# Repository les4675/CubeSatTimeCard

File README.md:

Currently we have developed models from the top level overview of our time card, along with setting up the SOM. Our goal in the next few months is program the SOM to take in data from a GNSS through the CAN protcol and to fine tone the PLL with the atomic clock that we have aquired.

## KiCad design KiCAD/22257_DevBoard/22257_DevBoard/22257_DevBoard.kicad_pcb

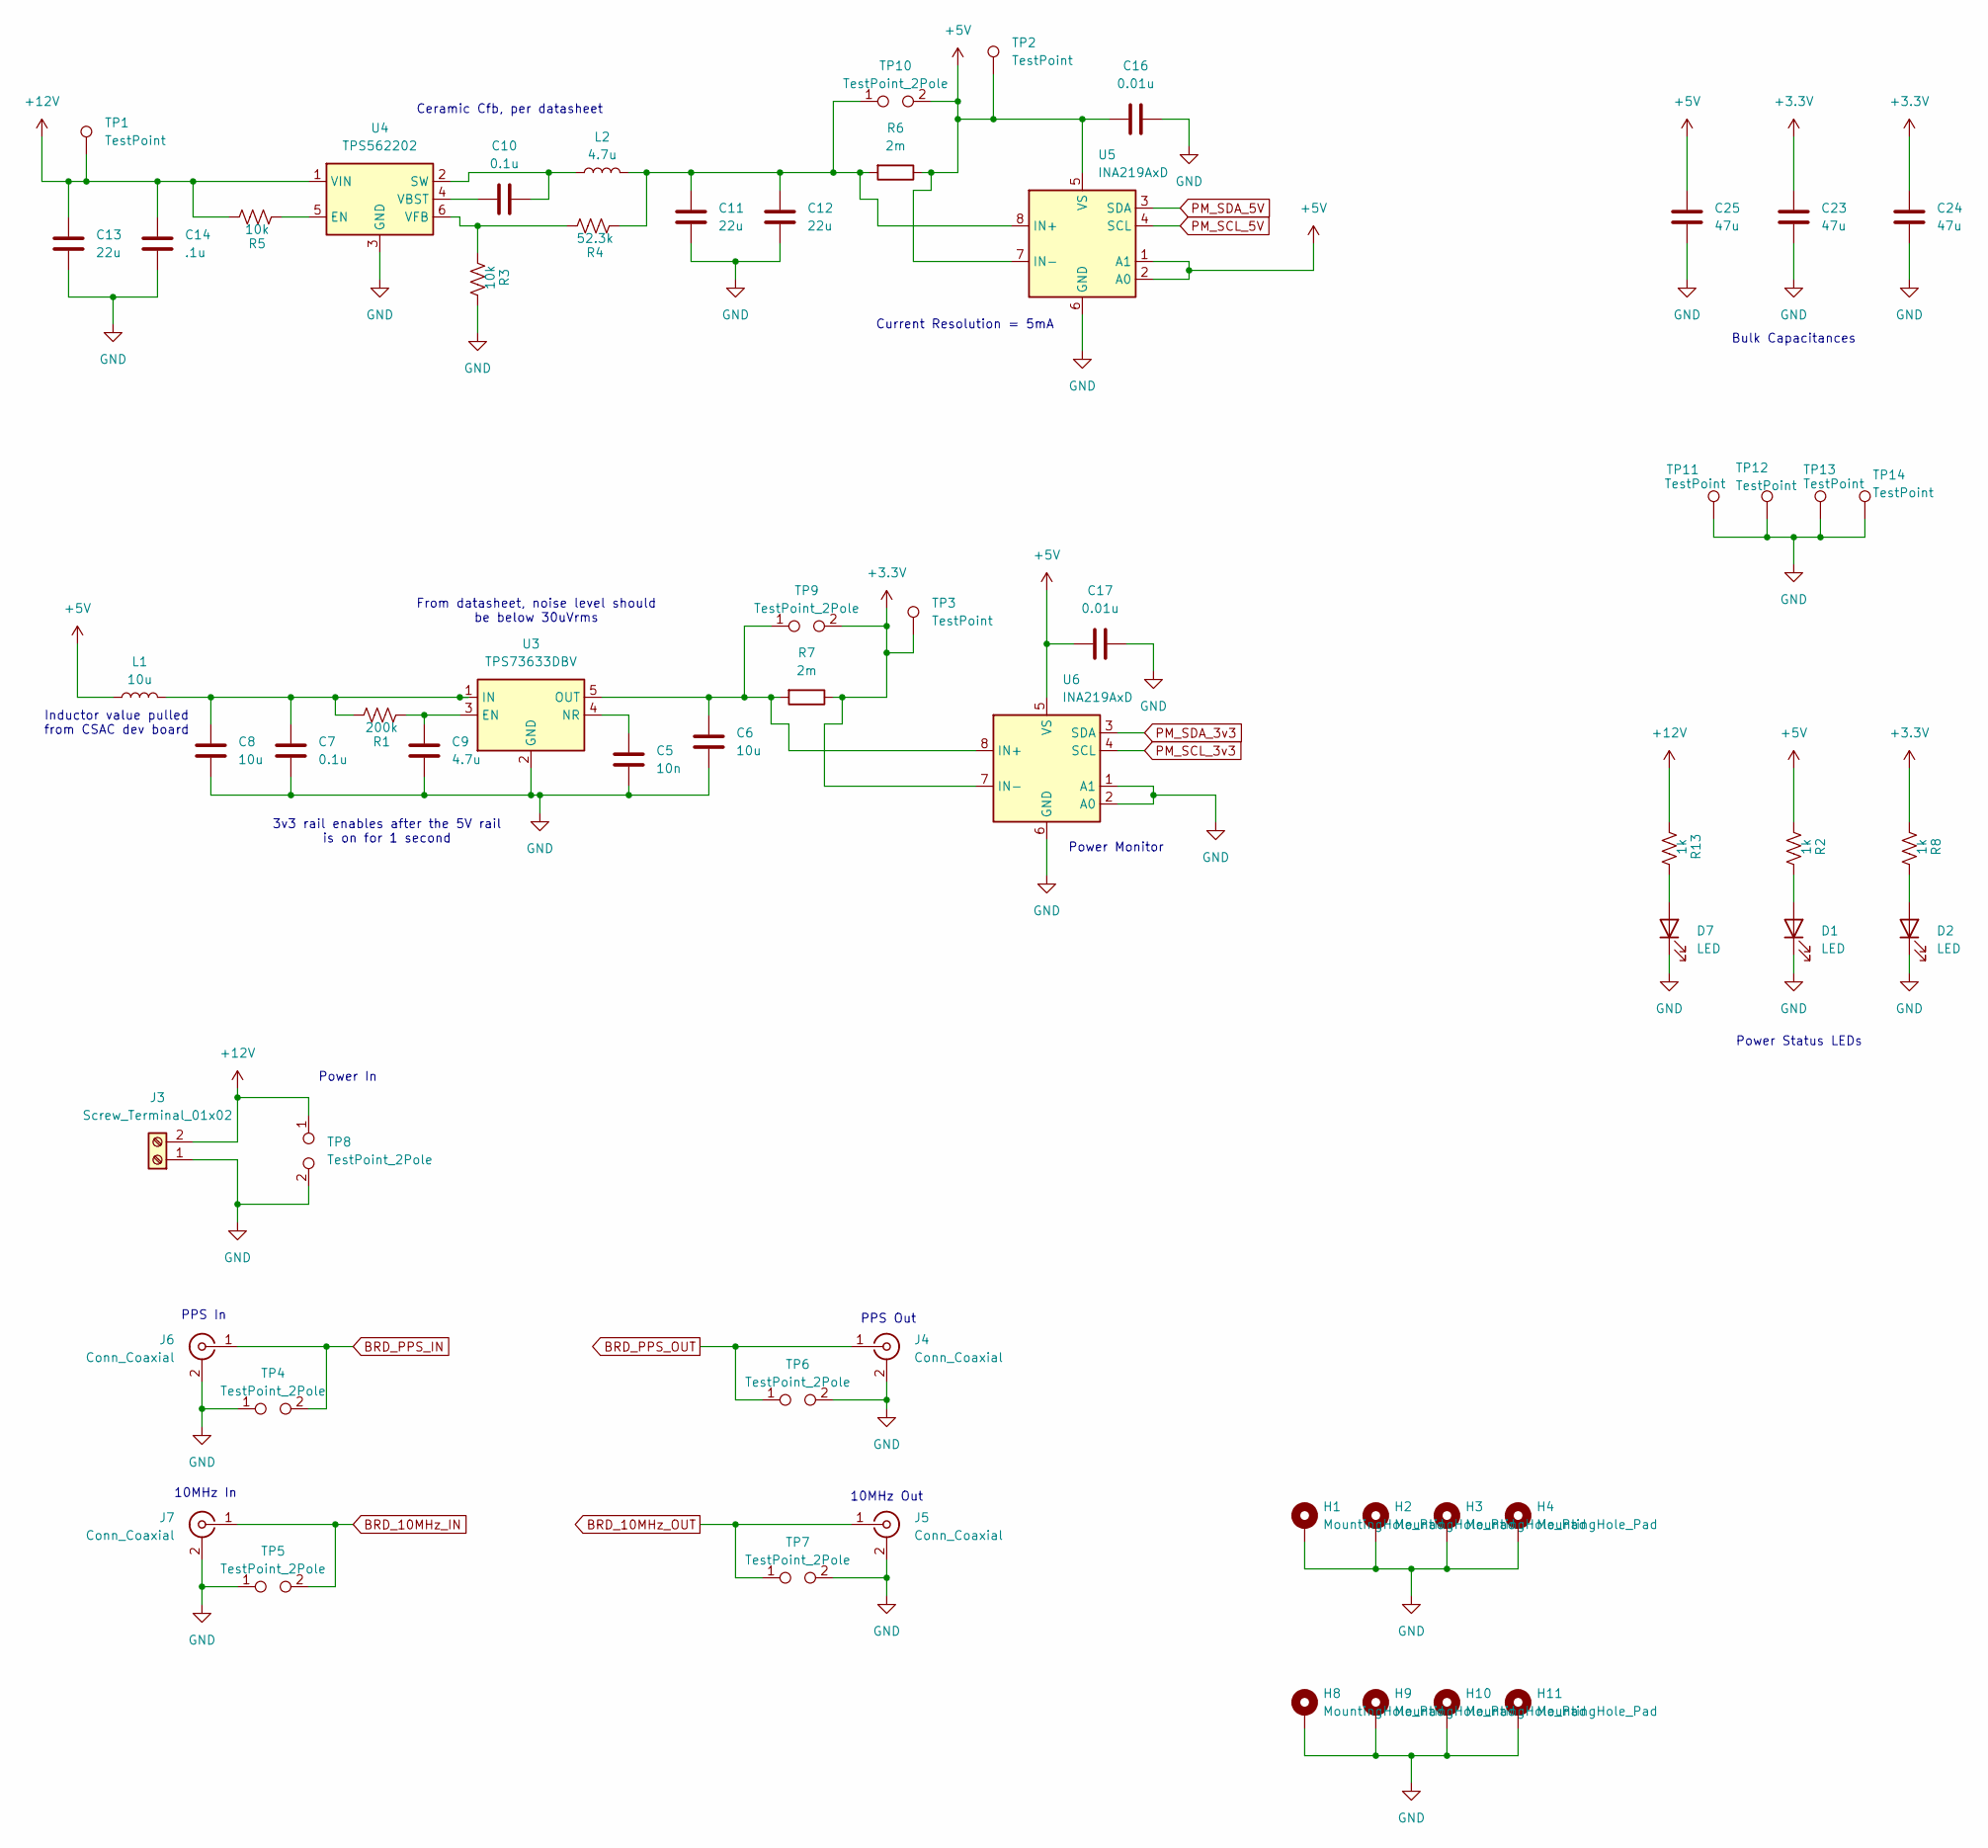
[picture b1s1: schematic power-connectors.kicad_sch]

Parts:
C5: 10n; C_0603_1608Metric
C6, C8: 10u; C_0603_1608Metric
C7, C10: 0.1u; C_0603_1608Metric
C9: 4.7u; C_0603_1608Metric
C11, C12, C13: 22u; C_0603_1608Metric
C14: .1u; C_0603_1608Metric
C16, C17: 0.01u; C_0603_1608Metric
C23, C24, C25: 47u; C_0603_1608Metric
D1, D2, D7: LED; LED_0603_1608Metric
H1, H2, H3, H4, H8, H9, H10, H11: MountingHole_Pad; MountingHole_3.2mm_M3_Pad
J3: Screw_Terminal_01x02; PhoenixContact_GMSTBA_2,5_2-G-7,62_1x02_P7.62mm_Horizontal
J4, J5, J6, J7: Conn_Coaxial; SMA_Amphenol_901-143_Horizontal
L1: 10u; L_Bourns-SRU8043
L2: 4.7u; L_Bourns-SRU8043
R1: 200k; R_0603_1608Metric
R2, R8, R13: 1k; R_0603_1608Metric
R3, R5: 10k; R_0603_1608Metric
R4: 52.3k; R_0603_1608Metric
R6, R7: 2m; BVT-I-R0002-1
TP1, TP2, TP3, TP11, TP12, TP13, TP14: TestPoint; TestPoint_THTPad_2.5x2.5mm_Drill1.2mm
TP4, TP5, TP6, TP7, TP8, TP9, TP10: TestPoint_2Pole; TestPoint_2Pads_Pitch5.08mm_Drill1.3mm
U3: TPS73633DBV; SOT-23-5
U4: TPS562202; SOT-563
U5, U6: INA219AxD; SOIC-8_3.9x4.9mm_P1.27mm

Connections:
+3.3V: C23.2, C24.2, R7.1, R8.2, TP3.1, TP9.2, U6.7 (IN-); also elsewhere on the board
+5V: C16.1, C17.1, C25.2, L1.1, R2.2, R6.1, TP2.1, TP10.2, U5.1 (A1), U5.2 (A0), U5.5 (VS), U5.7 (IN-), U6.5 (VS); also elsewhere on the board
+12V: C13.2, C14.2, J3.2, R5.1, R13.2, TP1.1, TP8.1, U4.1 (VIN)
BRD_10MHz_IN: J7.1 (In), TP5.2; also elsewhere on the board
BRD_10MHz_OUT: J5.1 (In), TP7.1; also elsewhere on the board
BRD_PPS_IN: J6.1 (In), TP4.2; also elsewhere on the board
BRD_PPS_OUT: J4.1 (In), TP6.1; also elsewhere on the board
GND: C5.2, C6.2, C7.2, C8.2, C9.2, C11.1, C12.1, C13.1, C14.1, C16.2, C17.2, C23.1, C24.1, C25.1, D1.1 (K), D2.1 (K), D7.1 (K), H1.1, H2.1, H3.1, H4.1, H8.1, H9.1, H10.1, H11.1, J3.1, J4.2 (Ext), J5.2 (Ext), J6.2 (Ext), J7.2 (Ext), R3.1, TP4.1, TP5.1, TP6.2, TP7.2, TP8.2, TP11.1, TP12.1, TP13.1, TP14.1, U3.2 (GND), U4.3 (GND), U5.6 (GND), U6.1 (A1), U6.2 (A0), U6.6 (GND); also elsewhere on the board
unnamed: D1.2 (A), R2.1
unnamed: D2.2 (A), R8.1
unnamed: D7.2 (A), R13.1
unnamed: C9.1, R1.2, U3.3 (EN)
unnamed: C7.1, C8.1, L1.2, R1.1, U3.1 (IN)
unnamed: C5.1, U3.4 (NR)
unnamed: C6.1, R7.2, TP9.1, U3.5 (OUT), U6.8 (IN+)
unnamed: R5.2, U4.5 (EN)
unnamed: C10.2, L2.1, U4.2 (SW)
unnamed: C10.1, U4.4 (VBST)
unnamed: R3.2, R4.1, U4.6 (VFB)
unnamed: C11.2, C12.2, L2.2, R4.2, R6.2, TP10.1, U5.8 (IN+)
PM_SCL_3v3: U6.4 (SCL); also elsewhere on the board
PM_SCL_5V: U5.4 (SCL); also elsewhere on the board
PM_SDA_3v3: U6.3 (SDA); also elsewhere on the board
PM_SDA_5V: U5.3 (SDA); also elsewhere on the board

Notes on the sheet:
10MHz Out
Power Status LEDs
3v3 rail enables after the 5V rail is on for 1 second
Power In
PPS In
Ceramic Cfb, per datasheet
From datasheet, noise level should be below 30uVrms
Current Resolution = 5mA
Power Monitor
PPS Out
Inductor value pulled from CSAC dev board
10MHz In
Bulk Capacitances

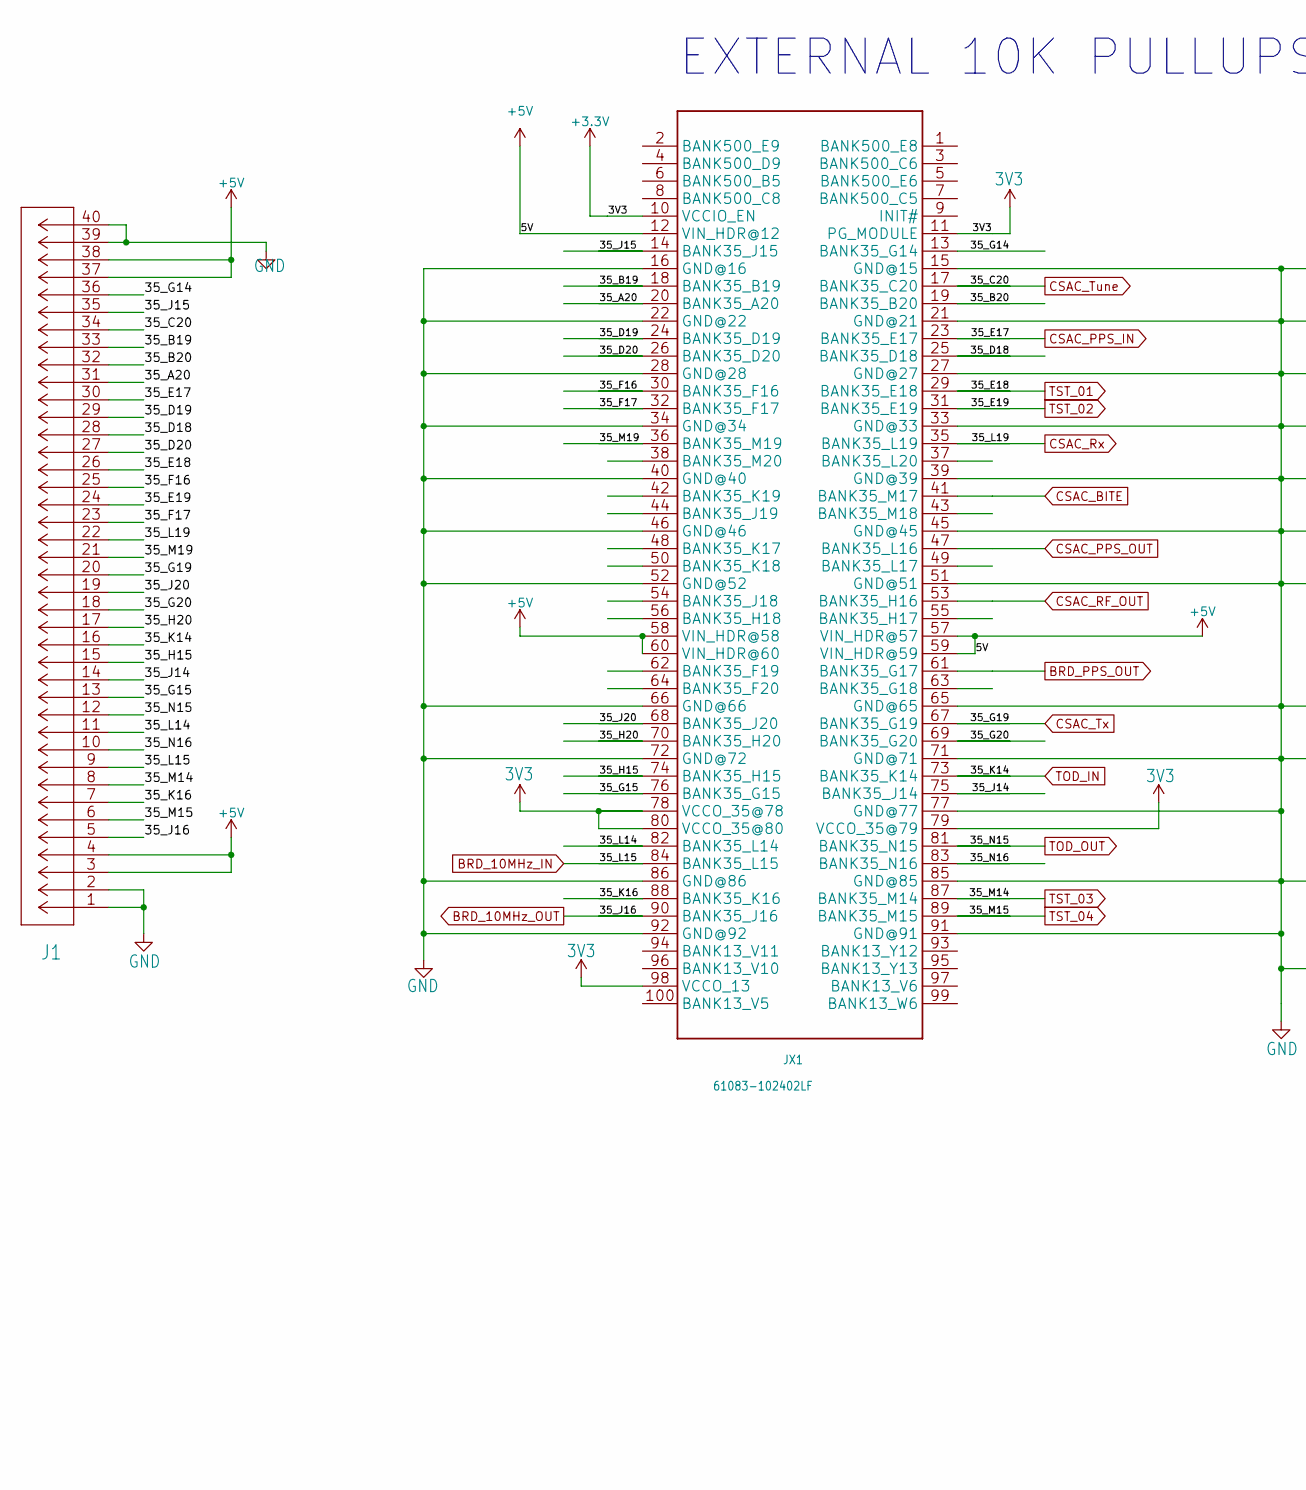
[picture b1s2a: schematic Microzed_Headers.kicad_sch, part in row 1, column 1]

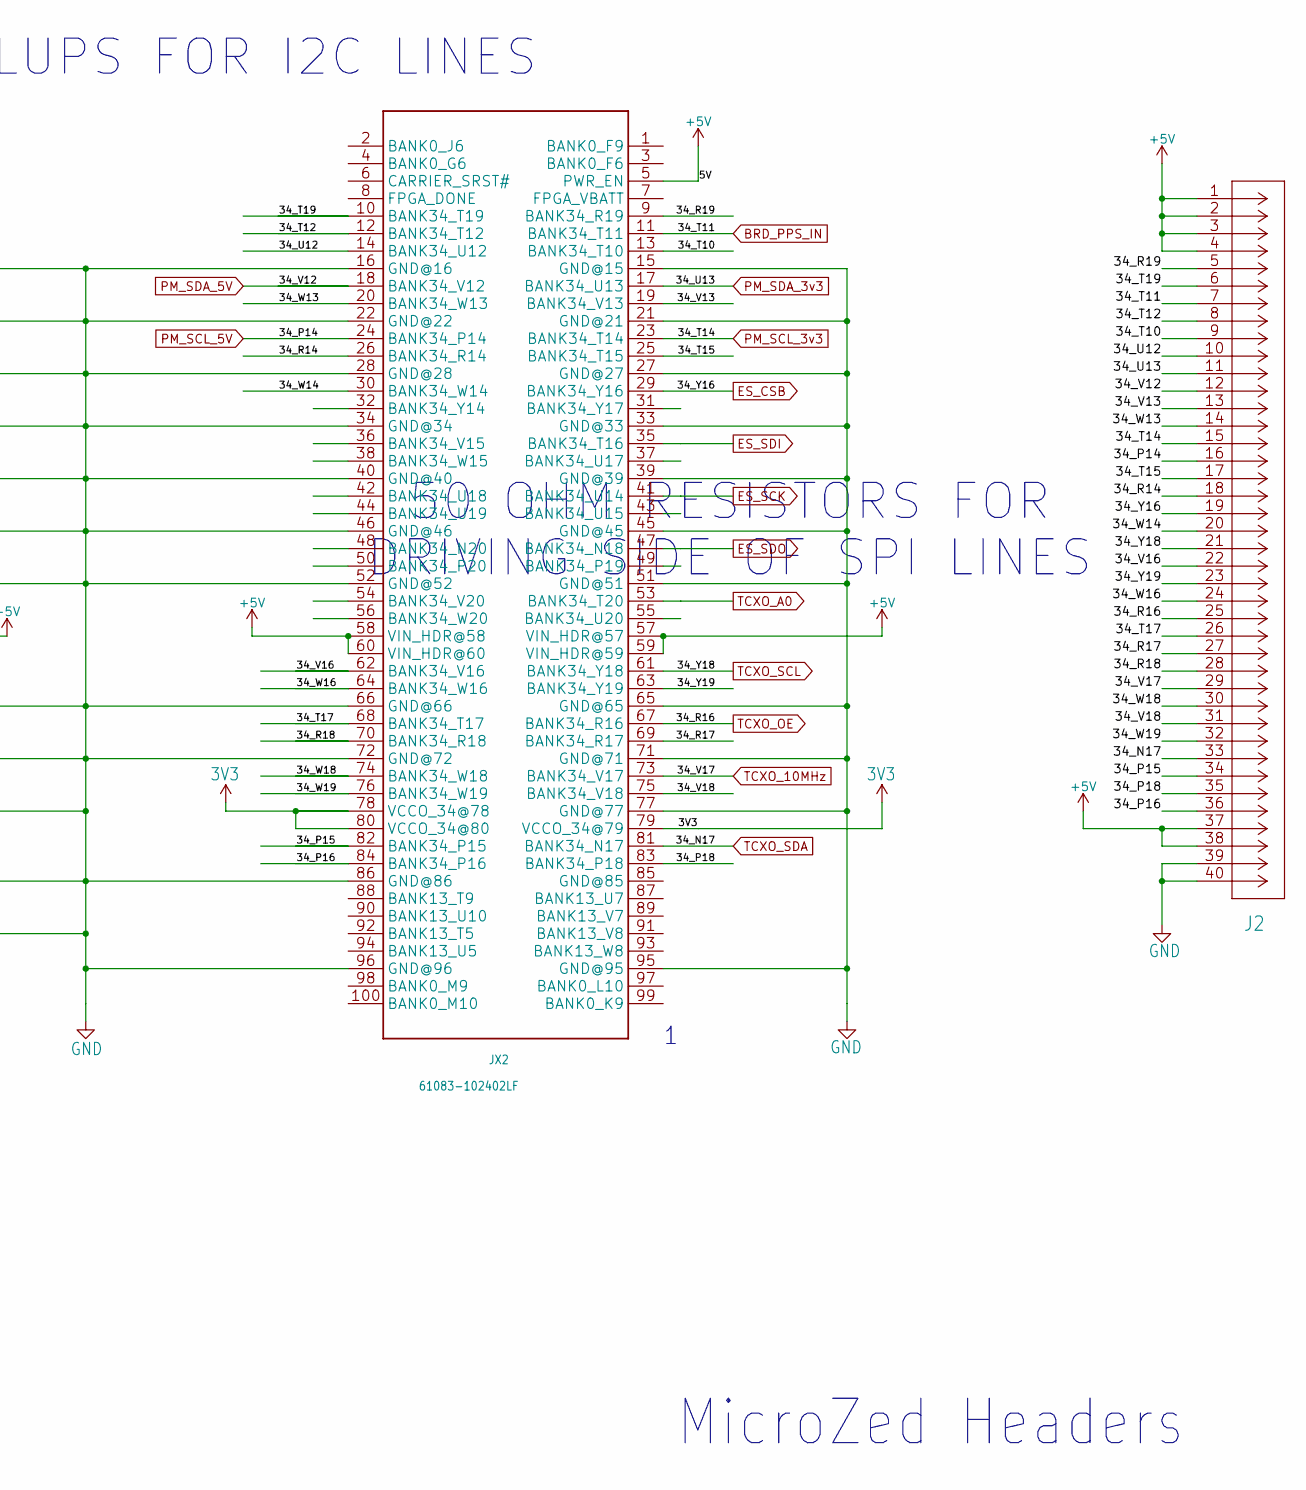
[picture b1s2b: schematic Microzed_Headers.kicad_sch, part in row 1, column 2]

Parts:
J1, J2: TD-120-G-AACON40_2X20_TU_HTS_SAI; CON40_2X20_TU_HTS_SAI
JX1, JX2: 61083-102402LF; 61083-102402LF_1104291

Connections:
+3.3V: JX1.10 (VCCIO_EN), JX1.11 (PG_MODULE), JX1.78 (VCCO_35@78), JX1.79 (VCCO_35@79), JX1.80 (VCCO_35@80), JX1.98 (VCCO_13), JX2.78 (VCCO_34@78), JX2.79 (VCCO_34@79), JX2.80 (VCCO_34@80); also elsewhere on the board
+5V: J1.3, J1.4, J1.37, J1.38, J2.1, J2.2, J2.3, J2.4, J2.37, J2.38, JX1.12 (VIN_HDR@12), JX1.57 (VIN_HDR@57), JX1.58 (VIN_HDR@58), JX1.59 (VIN_HDR@59), JX1.60 (VIN_HDR@60), JX2.5 (PWR_EN), JX2.57 (VIN_HDR@57), JX2.58 (VIN_HDR@58), JX2.59 (VIN_HDR@59), JX2.60 (VIN_HDR@60); also elsewhere on the board
/MicroZed_Headers/34_P15: J2.34, JX2.82 (BANK34_P15)
/MicroZed_Headers/34_P16: J2.36, JX2.84 (BANK34_P16)
/MicroZed_Headers/34_P18: J2.35, JX2.83 (BANK34_P18)
/MicroZed_Headers/34_R14: J2.18, JX2.26 (BANK34_R14)
/MicroZed_Headers/34_R17: J2.27, JX2.69 (BANK34_R17)
/MicroZed_Headers/34_R18: J2.28, JX2.70 (BANK34_R18)
/MicroZed_Headers/34_R19: J2.5, JX2.9 (BANK34_R19)
/MicroZed_Headers/34_T10: J2.9, JX2.13 (BANK34_T10)
/MicroZed_Headers/34_T12: J2.8, JX2.12 (BANK34_T12)
/MicroZed_Headers/34_T15: J2.17, JX2.25 (BANK34_T15)
/MicroZed_Headers/34_T17: J2.26, JX2.68 (BANK34_T17)
/MicroZed_Headers/34_T19: J2.6, JX2.10 (BANK34_T19)
/MicroZed_Headers/34_U12: J2.10, JX2.14 (BANK34_U12)
/MicroZed_Headers/34_V13: J2.13, JX2.19 (BANK34_V13)
/MicroZed_Headers/34_V16: J2.22, JX2.62 (BANK34_V16)
/MicroZed_Headers/34_V18: J2.31, JX2.75 (BANK34_V18)
/MicroZed_Headers/34_W13: J2.14, JX2.20 (BANK34_W13)
/MicroZed_Headers/34_W14: J2.20, JX2.30 (BANK34_W14)
/MicroZed_Headers/34_W16: J2.24, JX2.64 (BANK34_W16)
/MicroZed_Headers/34_W18: J2.30, JX2.74 (BANK34_W18)
/MicroZed_Headers/34_W19: J2.32, JX2.76 (BANK34_W19)
/MicroZed_Headers/34_Y19: J2.23, JX2.63 (BANK34_Y19)
/MicroZed_Headers/35_A20: J1.31, JX1.20 (BANK35_A20)
/MicroZed_Headers/35_B19: J1.33, JX1.18 (BANK35_B19)
/MicroZed_Headers/35_B20: J1.32, JX1.19 (BANK35_B20)
/MicroZed_Headers/35_D18: J1.28, JX1.25 (BANK35_D18)
/MicroZed_Headers/35_D19: J1.29, JX1.24 (BANK35_D19)
/MicroZed_Headers/35_D20: J1.27, JX1.26 (BANK35_D20)
/MicroZed_Headers/35_F16: J1.25, JX1.30 (BANK35_F16)
/MicroZed_Headers/35_F17: J1.23, JX1.32 (BANK35_F17)
/MicroZed_Headers/35_G14: J1.36, JX1.13 (BANK35_G14)
/MicroZed_Headers/35_G15: J1.13, JX1.76 (BANK35_G15)
/MicroZed_Headers/35_G20: J1.18, JX1.69 (BANK35_G20)
/MicroZed_Headers/35_H15: J1.15, JX1.74 (BANK35_H15)
/MicroZed_Headers/35_H20: J1.17, JX1.70 (BANK35_H20)
/MicroZed_Headers/35_J14: J1.14, JX1.75 (BANK35_J14)
/MicroZed_Headers/35_J15: J1.35, JX1.14 (BANK35_J15)
/MicroZed_Headers/35_J20: J1.19, JX1.68 (BANK35_J20)
/MicroZed_Headers/35_K16: J1.7, JX1.88 (BANK35_K16)
/MicroZed_Headers/35_L14: J1.11, JX1.82 (BANK35_L14)
/MicroZed_Headers/35_M19: J1.21, JX1.36 (BANK35_M19)
/MicroZed_Headers/35_N16: J1.10, JX1.83 (BANK35_N16)
BRD_10MHz_IN: J1.9, JX1.84 (BANK35_L15); also elsewhere on the board
BRD_10MHz_OUT: J1.5, JX1.90 (BANK35_J16); also elsewhere on the board
BRD_PPS_IN: J2.7, JX2.11 (BANK34_T11); also elsewhere on the board
BRD_PPS_OUT: JX1.61 (BANK35_G17); also elsewhere on the board
CSAC_BITE: JX1.41 (BANK35_M17); also elsewhere on the board
CSAC_PPS_IN: J1.30, JX1.23 (BANK35_E17); also elsewhere on the board
CSAC_PPS_OUT: JX1.47 (BANK35_L16); also elsewhere on the board
CSAC_RF_OUT: JX1.53 (BANK35_H16); also elsewhere on the board
CSAC_Rx: J1.22, JX1.35 (BANK35_L19); also elsewhere on the board
CSAC_Tune: J1.34, JX1.17 (BANK35_C20); also elsewhere on the board
CSAC_Tx: J1.20, JX1.67 (BANK35_G19); also elsewhere on the board
ES_CSB: J2.19, JX2.29 (BANK34_Y16); also elsewhere on the board
ES_SCK: JX2.41 (BANK34_U14); also elsewhere on the board
ES_SDI: JX2.35 (BANK34_T16); also elsewhere on the board
ES_SDO: JX2.47 (BANK34_N18)
GND: J1.1, J1.2, J1.39, J1.40, J2.39, J2.40, JX1.15 (GND@15), JX1.16 (GND@16), JX1.21 (GND@21), JX1.22 (GND@22), JX1.27 (GND@27), JX1.28 (GND@28), JX1.33 (GND@33), JX1.34 (GND@34), JX1.39 (GND@39), JX1.40 (GND@40), JX1.45 (GND@45), JX1.46 (GND@46), JX1.51 (GND@51), JX1.52 (GND@52), JX1.65 (GND@65), JX1.66 (GND@66), JX1.71 (GND@71), JX1.72 (GND@72), JX1.77 (GND@77), JX1.85 (GND@85), JX1.86 (GND@86), JX1.91 (GND@91), JX1.92 (GND@92), JX2.15 (GND@15), JX2.16 (GND@16), JX2.21 (GND@21), JX2.22 (GND@22), JX2.27 (GND@27), JX2.28 (GND@28), JX2.33 (GND@33), JX2.34 (GND@34), JX2.39 (GND@39), JX2.40 (GND@40), JX2.45 (GND@45), JX2.46 (GND@46), JX2.51 (GND@51), JX2.52 (GND@52), JX2.65 (GND@65), JX2.66 (GND@66), JX2.71 (GND@71), JX2.72 (GND@72), JX2.77 (GND@77), JX2.86 (GND@86), JX2.95 (GND@95), JX2.96 (GND@96); also elsewhere on the board
PM_SCL_3v3: J2.15, JX2.23 (BANK34_T14); also elsewhere on the board
PM_SCL_5V: J2.16, JX2.24 (BANK34_P14); also elsewhere on the board
PM_SDA_3v3: J2.11, JX2.17 (BANK34_U13); also elsewhere on the board
PM_SDA_5V: J2.12, JX2.18 (BANK34_V12); also elsewhere on the board
TCXO_10MHz: J2.29, JX2.73 (BANK34_V17); also elsewhere on the board
TCXO_A0: JX2.53 (BANK34_T20)
TCXO_OE: J2.25, JX2.67 (BANK34_R16); also elsewhere on the board
TCXO_SCL: J2.21, JX2.61 (BANK34_Y18); also elsewhere on the board
TCXO_SDA: J2.33, JX2.81 (BANK34_N17); also elsewhere on the board
TOD_IN: J1.16, JX1.73 (BANK35_K14)
TOD_OUT: J1.12, JX1.81 (BANK35_N15)
TST_01: J1.26, JX1.29 (BANK35_E18); also elsewhere on the board
TST_02: J1.24, JX1.31 (BANK35_E19); also elsewhere on the board
TST_03: J1.8, JX1.87 (BANK35_M14); also elsewhere on the board
TST_04: J1.6, JX1.89 (BANK35_M15); also elsewhere on the board

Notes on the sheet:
EXTERNAL 10K PULLUPS FOR I2C LINES
MicroZed Headers
50 OHM RESISTORS FOR DRIVING SIDE OF SPI LINES

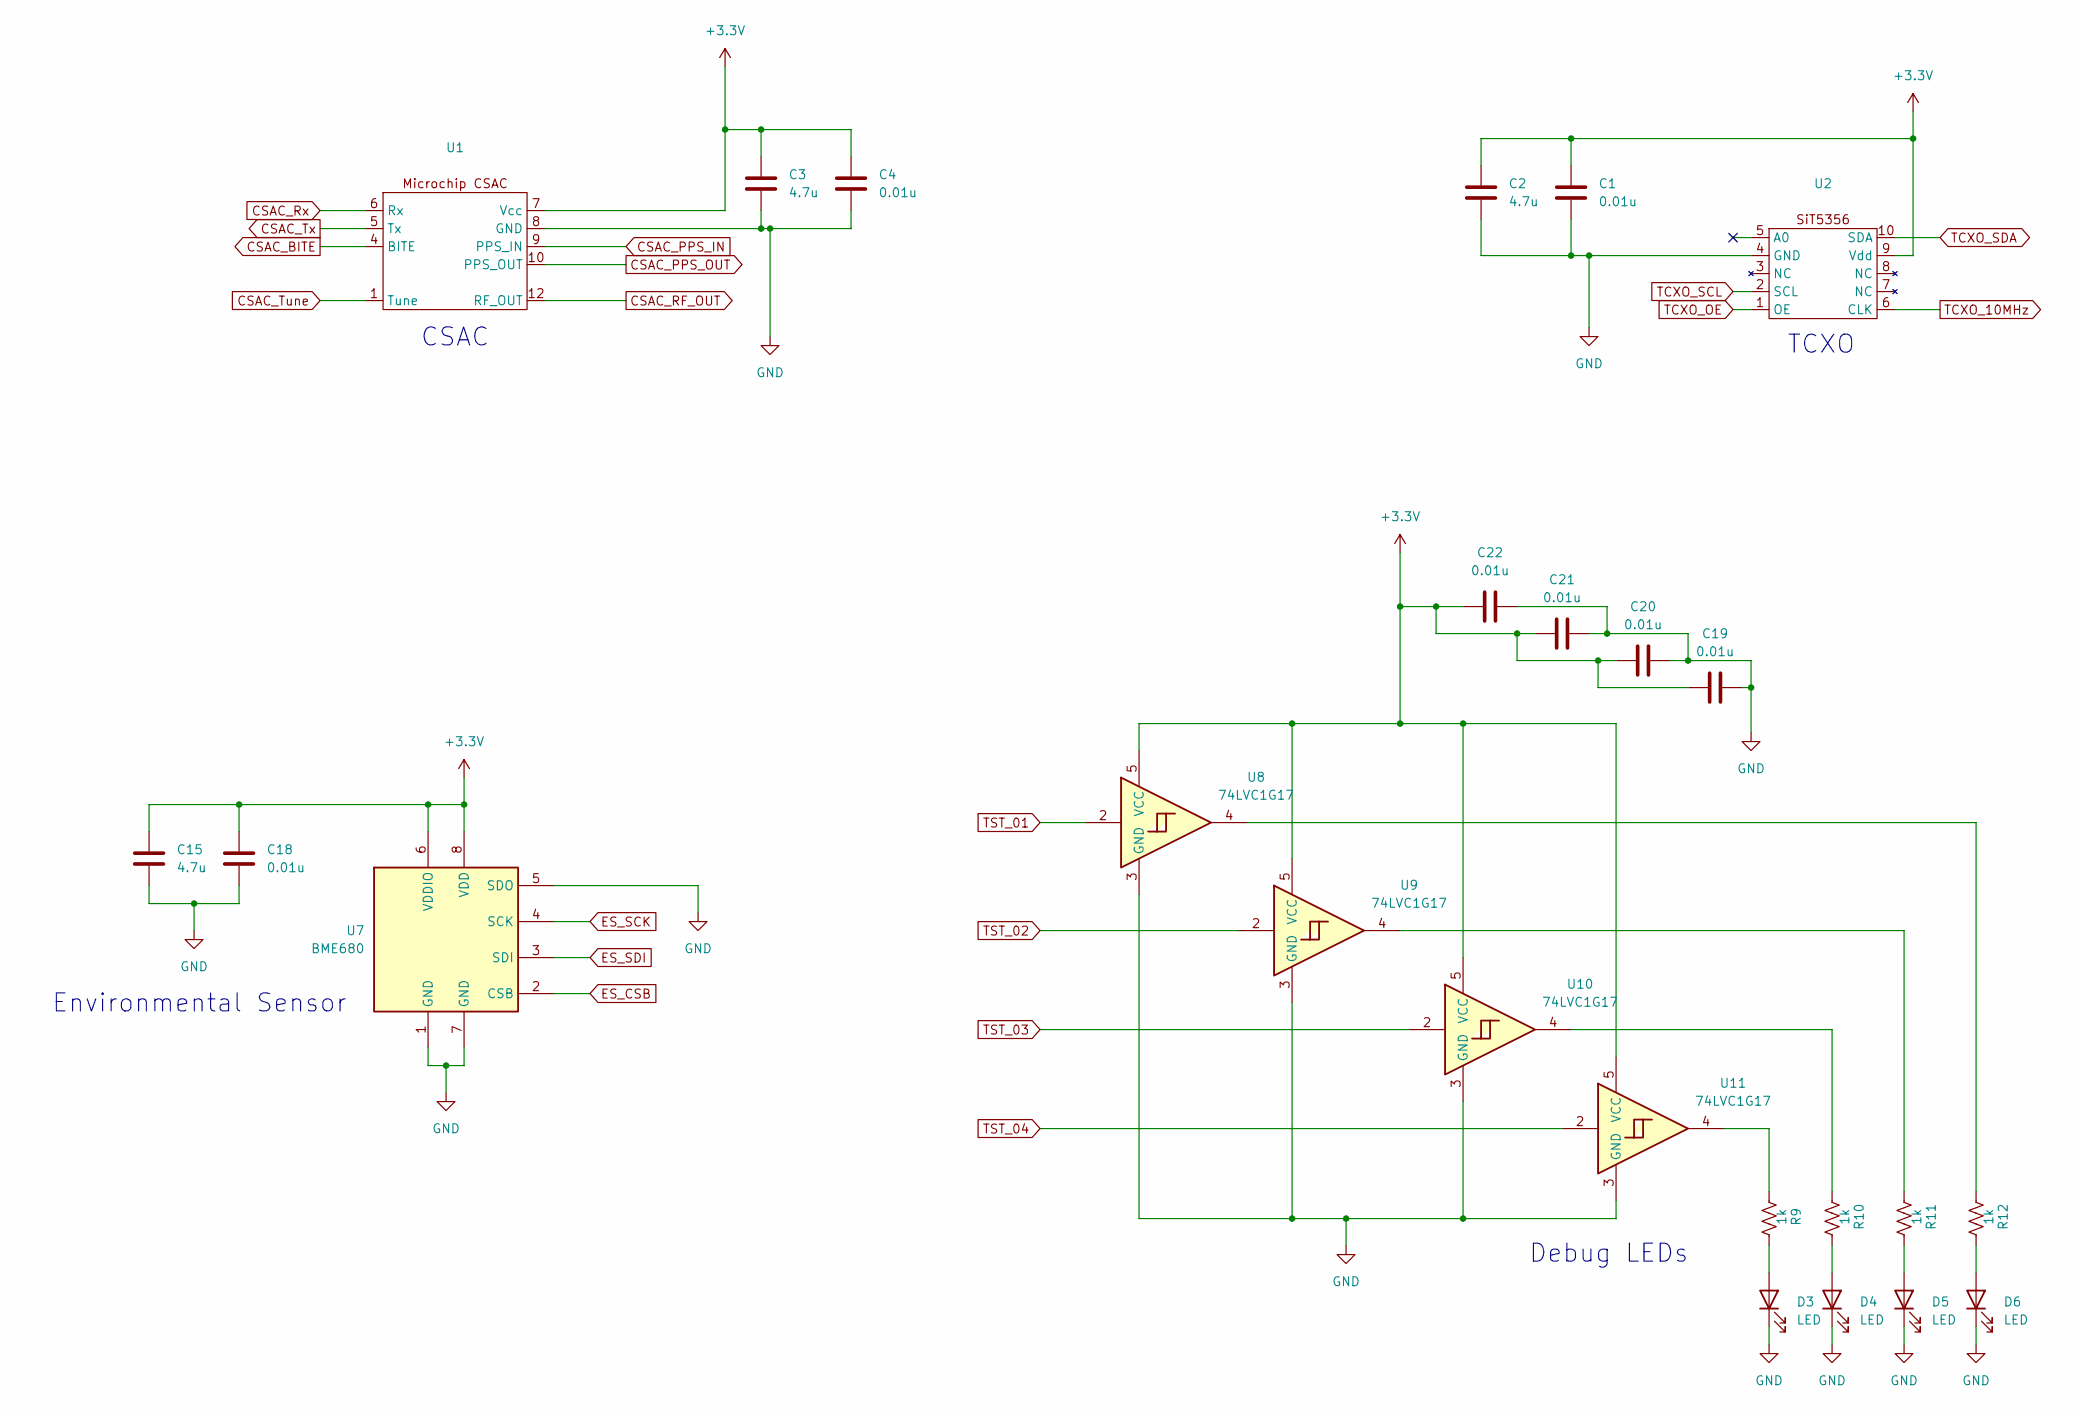
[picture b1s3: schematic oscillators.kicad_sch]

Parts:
C1, C4, C18, C19, C20, C21, C22: 0.01u; C_0603_1608Metric
C2, C3, C15: 4.7u; C_0603_1608Metric
D3, D4, D5, D6: LED; LED_0603_1608Metric
R9, R10, R11, R12: 1k; R_0603_1608Metric
U1: SA-45
U2: SiT5356
U7: BME680; Bosch_LGA-8_3x3mm_P0.8mm_ClockwisePinNumbering
U8, U9, U10, U11: 74LVC1G17; SOT-23-5_HandSoldering

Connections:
+3.3V: C1.1, C2.1, C3.1, C4.1, C15.1, C18.1, C19.1, C20.1, C21.1, C22.1, U1.7 (Vcc), U2.9 (Vdd), U7.6 (VDDIO), U7.8 (VDD), U8.5 (VCC), U9.5 (VCC), U10.5 (VCC), U11.5 (VCC); also elsewhere on the board
CSAC_BITE: U1.4 (BITE); also elsewhere on the board
CSAC_PPS_IN: U1.9 (PPS_IN); also elsewhere on the board
CSAC_PPS_OUT: U1.10 (PPS_OUT); also elsewhere on the board
CSAC_RF_OUT: U1.12 (RF_OUT); also elsewhere on the board
CSAC_Rx: U1.6 (Rx); also elsewhere on the board
CSAC_Tune: U1.1 (Tune); also elsewhere on the board
CSAC_Tx: U1.5 (Tx); also elsewhere on the board
ES_CSB: U7.2 (CSB); also elsewhere on the board
ES_SCK: U7.4 (SCK); also elsewhere on the board
ES_SDI: U7.3 (SDI); also elsewhere on the board
GND: C1.2, C2.2, C3.2, C4.2, C15.2, C18.2, C19.2, C20.2, C21.2, C22.2, D3.1 (K), D4.1 (K), D5.1 (K), D6.1 (K), U1.8 (GND), U2.4 (GND), U7.1 (GND), U7.5 (SDO), U7.7 (GND), U8.3 (GND), U9.3 (GND), U10.3 (GND), U11.3 (GND); also elsewhere on the board
unnamed: D3.2 (A), R9.1
unnamed: D4.2 (A), R10.1
unnamed: D5.2 (A), R11.1
unnamed: D6.2 (A), R12.1
unnamed: R9.2, U11.4
unnamed: R10.2, U10.4
unnamed: R11.2, U9.4
unnamed: R12.2, U8.4
TCXO_10MHz: U2.6 (CLK); also elsewhere on the board
TCXO_OE: U2.1 (OE); also elsewhere on the board
TCXO_SCL: U2.2 (SCL); also elsewhere on the board
TCXO_SDA: U2.10 (SDA); also elsewhere on the board
TST_01: U8.2; also elsewhere on the board
TST_02: U9.2; also elsewhere on the board
TST_03: U10.2; also elsewhere on the board
TST_04: U11.2; also elsewhere on the board

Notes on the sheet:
Environmental Sensor
Debug LEDs
TCXO
CSAC

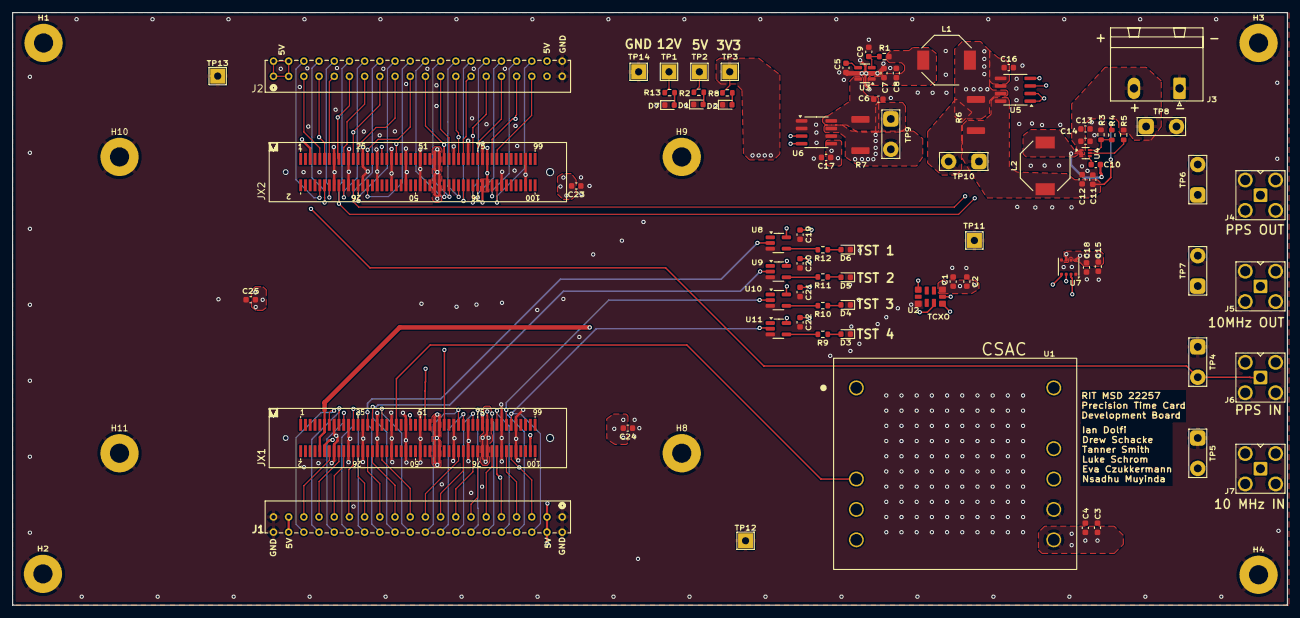
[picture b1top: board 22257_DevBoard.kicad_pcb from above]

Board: 6 copper layers, 213.1 x 99.1 mm, 89 parts (0 on the bottom side), 94 nets.

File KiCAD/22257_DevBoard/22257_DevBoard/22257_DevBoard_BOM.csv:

"Reference","Value","Datasheet","Footprint","Qty","DNP"
"C1,C4,C16,C17,C18,C19,C20,C21,C22","0.01u","~","Capacitor_SMD:C_0603_1608Metric","9",""
"C2,C3,C9,C15,L2","4.7u","~","Capacitor_SMD:C_0603_1608Metric,Inductor_SMD:L_Bourns-SRU8043","5",""
"C5","10n","~","Capacitor_SMD:C_0603_1608Metric","1",""
"C6,C8,L1","10u","~","Capacitor_SMD:C_0603_1608Metric,Inductor_SMD:L_Bourns-SRU8043","3",""
"C7,C10","0.1u","~","Capacitor_SMD:C_0603_1608Metric","2",""
"C11,C12,C13","22u","~","Capacitor_SMD:C_0603_1608Metric","3",""
"C14",".1u","~","Capacitor_SMD:C_0603_1608Metric","1",""
"C23,C24,C25","47u","~","Capacitor_SMD:C_0603_1608Metric","3",""
"D1,D2,D3,D4,D5,D6,D7","LED","~","LED_SMD:LED_0603_1608Metric","7",""
"J1,J2","TD-120-G-AACON40_2X20_TU_HTS_SAI","","22257_DevBoard:CON40_2X20_TU_HTS_SAI","2",""
"J3","Screw_Terminal_01x02","~","Connector_Phoenix_GMSTB:PhoenixContact_GMSTBA_2,5_2-G-7,62_1x02_P7.62mm_Horizontal","1",""
"J4,J5,J6,J7","Conn_Coaxial","~","Connector_Coaxial:SMA_Amphenol_901-143_Horizontal","4",""
"JX1,JX2","61083-102402LF","","22257_DevBoard:61083-102402LF_1104291","2",""
"R1","200k","~","Resistor_SMD:R_0603_1608Metric","1",""
"R2,R8,R9,R10,R11,R12,R13","1k","~","Resistor_SMD:R_0603_1608Metric","7",""
"R3,R5","10k","~","Resistor_SMD:R_0603_1608Metric","2",""
"R4","52.3k","~","Resistor_SMD:R_0603_1608Metric","1",""
"R6,R7","2m","~","2222_DevBoar_Footprints:BVT-I-R0002-1","2",""
"TP1,TP2,TP3,TP11,TP12,TP13,TP14","TestPoint","~","TestPoint:TestPoint_THTPad_2.5x2.5mm_Drill1.2mm","7",""
"TP4,TP5,TP6,TP7,TP8,TP9,TP10","TestPoint_2Pole","~","TestPoint:TestPoint_2Pads_Pitch5.08mm_Drill1.3mm","7",""
"U3","TPS73633DBV","http://www.ti.com/lit/ds/symlink/tps736.pdf","Package_TO_SOT_SMD:SOT-23-5","1",""
"U4","TPS562202","https://www.ti.com/lit/gpn/tps562202","Package_TO_SOT_SMD:SOT-563","1",""
"U5,U6","INA219AxD","http://www.ti.com/lit/ds/symlink/ina219.pdf","Package_SO:SOIC-8_3.9x4.9mm_P1.27mm","2",""
"U7","BME680","https://ae-bst.resource.bosch.com/media/_tech/media/datashee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","Package_LGA:Bosch_LGA-8_3x3mm_P0.8mm_ClockwisePinNumbering","1",""
"U8,U9,U10,U11","74LVC1G17","https://www.ti.com/lit/ds/symlink/sn74lvc1g17.pdf","Package_TO_SOT_SMD:SOT-23-5_HandSoldering","4",""
